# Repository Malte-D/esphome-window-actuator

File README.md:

# ESPHome Tilt Window Opener

<p align="center">

</p>

Motorise an ordinary **tilt-and-turn window** (German: *Dreh-Kipp-Fenster*) with two
3D-printed units, two 12 V servos (DSSERVO DS51150, 150 kg·cm) and an ESP8266 running [ESPHome](https://esphome.io).
The window shows up in Home Assistant as a `cover` and can be tilted open and closed
again, including turning the handle. No drilling: the handle unit uses the original
handle screws and the top unit is hot-glued.

<p align="center">
  
  <br/>
  <sub>Rendered animation. The inset shows the handle unit cut open, then the linkage at the top of the sash.
  <a href="docs/media/demo.mp4">Full resolution video</a></sub>
</p>

> **Status: v0.1.** The hardware and firmware have been in daily use for more than a year.
> Places that still need a value are marked **TBD**; values marked *(estimate)* were derived from
> the CAD files and still need to be confirmed.

## Features

- Tilts the window open and closes it again from Home Assistant (`cover` entity, device class `window`)
- Turns the handle by itself: closed ↔ tilt, plus a "fully open" (turn) position
- Servo power is switched by a relay only while something moves: no humming or holding current when idle
- Maintenance mode to calibrate every end position from Home Assistant; values are stored on the device
- Bayonet quick release in the linkage, so the window can still be opened completely by hand
- Hot glue on the top unit doubles as a breakaway point if something jams
- Firmware can be flashed from the browser (ESP Web Tools) and adopted in the ESPHome dashboard

## How it works

The opener consists of two units on the sash, connected by a servo cable:

| | Handle unit | Top unit |
|---|---|---|
| Replaces / sits on | the window handle | the top rail of the sash |
| Servo | DS51150, 150 kg·cm, 12 V, **270° version** | DS51150, 150 kg·cm, 12 V, 180° or 270° version |
| Moves | the 7 mm square spindle of the window gear | an 80 mm arm, linked to a pivot glued into the corner between frame and lintel |
| Also contains | the [PCB](pcb/README.md) (Wemos D1 mini, relay, 5 V step-down converter) | – |

The original handle is removed. A short 7 mm square spindle goes from the window gear into
the **ServoHornAdapter**, which is screwed onto the servo horn on the same axis, so the servo
turns the spindle directly, like a hand on the handle. The handle servo is the 270° version of the DS51150:
the handle only needs 180°, the rest is margin for adjusting the end positions in software.

At the top, the servo arm and a short coupler with two rod ends (uniball joints) form a linkage
to a fixed pivot. When the arm swings round, it pushes the top of the sash into the room, and the
window tilts. The coupler is a printed bayonet, so the window can be disconnected from the arm
and opened completely by hand.

Sequence (see [`window-actuator-template-esp8266.yaml`](window-actuator-template-esp8266.yaml)):

| Open | Close |
|---|---|
| 1. Relay on (servo power) | 1. Relay on |
| 2. Handle servo → tilt position (3 s) | 2. Arm servo → closed position (2 s) |
| 3. Arm servo → open position (2 s) | 3. Handle servo → closed position (3 s) |
| 4. Relay off | 4. Relay off |

## What you need

### Window

A standard tilt-and-turn window with the usual handle fixing: two screws 43 mm apart and a
7 mm square spindle; handle down = closed, horizontal = turn, up = tilt. The top unit needs a
bit of visible frame between the top of the sash and the lintel for the arm and the pivot mount.

### Printed parts

All parts are in [`print-files/`](print-files) as STEP and (mostly) 3MF.

| Part | Folder | Qty | Notes |
|---|---|---|---|
| Base | `Handle` | 1 | Mounts with the original handle screws. 3MF: **TBD** |
| Case | `Handle` | 1 | Holds the handle servo and the PCB holder |
| ServoCover | `Handle` | 1 | Snaps onto the two CoverSnaps |
| CoverSnap | `Handle` | 2 | Clamped under the servo screws |
| PCBHolder | `Handle` | 1 | Slides into the slot at the edge of the base. 3MF: **TBD** |
| ServoHornAdapter | `Handle` | 1 | Square spindle → servo horn |
| ServoCoverMount | `Movement` | 1 | Housing for the arm servo, hooks over the top rail of the sash |
| NutHolder | `Movement` | 2 | Holds the M3 nuts behind the servo flange |
| ServoArm | `Movement` | 1 | 80 mm from servo axis to the M6 bolt |
| TopPivotMount *or* TopPivotMountChamfered | `Movement` | 1 | Pivot in the corner between frame and lintel. Use the chamfered version (45°) if that corner is not a clean right angle |
| BayonetSocket + BayonetPlug | `Movement` | 1 each | Quick release between the two rod ends. Both have a printed M6 thread for the rod ends |
| CableDuctCorner | `Accessories` | 2 | Corner for 16 × 8 mm half-round cable duct; the spigots go into the duct ends. One per bend, see [wiring](docs/assembly.md#6-wiring) |

The 3MF files contain only the geometry, no printer or slicer settings.

- **Material:** PLA is enough, even on a window in the sun.
- **Settings** *(estimate)*: 0.2 mm layers, 4 walls, 30–40 % infill for the parts that carry the
  servo torque (Base, Case, ServoHornAdapter, ServoArm, ServoCoverMount, bayonet), 20 % for the rest.
- Supports only where the slicer finds real overhangs; keep nut traps and slots free of support.

### Electronics

| Qty | Part | Notes |
|---|---|---|
| 2 | Servo **DSSERVO DS51150** (150 kg·cm, 12 V), e.g. [this one on AliExpress](https://www.aliexpress.com/item/1005006896077837.html) | 270° version for the handle; for the arm 180° is enough. The 12 V supply is why the 150 kg version is used: the smaller ones are specified below 12 V. The servo horn that comes with it is used |
| 1 | Custom PCB, 35 × 60 mm, with a Wemos D1 mini, a 5 V relay for the servo power and a 12 V → 5 V step-down converter | Gerbers, design files and parts list in [`pcb/`](pcb/README.md) |
| 1 | 12 V power supply, 5 A, standard plug 5.5 × 2.1 mm, centre positive | The prototype runs on a 12 V / 5 A supply. An angled plug fits best under the case |
| 1 | Servo extension cable | From the handle unit to the top unit (top centre of the sash); length depends on the window |
| – | Cable duct, half-round, 16 × 8 mm | Along the sash for both cables, see [wiring](docs/assembly.md#6-wiring). The prototype uses white D-Line duct with the printed CableDuctCorner at the bends |

### Hardware

| Qty | Part | Where |
|---|---|---|
| 1 | 7 mm square spindle, 50 mm on the prototype; the length depends on the window, see [below](#spindle-length) | Window gear → ServoHornAdapter |
| 2 | Original handle screws | Base → sash |
| 3 | M4×16 countersunk | Case → Base (from the side) |
| 3 | M4 square nut, DIN 562 (7 × 7 × 2.2 mm) | Slots in the base |
| 8 | M3×25 | 4 per servo: handle servo and CoverSnaps → Case, arm servo → ServoCoverMount |
| 8 | Rubber grommets, come with the servos | In the flange slots of both servos, to decouple vibrations |
| 8 | M3 nut | 4 in the case, 2 in each NutHolder |
| 4 | M3×10 countersunk | Servo horns (2 on the adapter, 2 on the arm) |
| 1 | M3×10 | PCB → PCBHolder |
| 2 | M6 rod end / uniball joint with male thread (e.g. SA6T/K or POSA6) | Screwed into the bayonet socket and plug |
| 1 | M6×25 + M6 nut | Rod end → ServoArm |
| 1 | M4×16 + M4 washer + M4 nut | Rod end → pin of the TopPivotMount |
| 1 | O-ring 10 × 2 mm | On the stem of the bayonet plug, keeps the bayonet locked |
| – | Hot glue | ServoCoverMount → sash, TopPivotMount → frame and lintel |

The servo horns are the ones that come with the DS51150 servos.

#### Spindle length

The spindle has to stick out about **21–25 mm from the surface of the sash** (where the handle
rosette was) *(estimate)*: the square hole in the ServoHornAdapter starts about 13 mm above the sash
and is 12.8 mm deep. These values come from the CAD files, a model of the DS51150 and the measured
7.5 mm between case and CoverSnap (rubber grommets under the servo flange), not from a measurement
of the spindle itself. How far the spindle goes into the window depends on the window. The prototype uses a
50 mm spindle; a longer one can be cut to length.

## Assembly

See the step-by-step guide in **[docs/assembly.md](docs/assembly.md)**.

## Firmware

### Install

1. Open the [installer page](https://malte-d.github.io/esphome-tilt-window-opener/) in Chrome or Edge,
   connect the D1 mini via USB and click **Install**.
2. Enter your Wi-Fi credentials in the installer (Improv). Alternatively, the device opens a
   fallback hotspot `window-actuator-xxxxxx`; its password is set in the YAML (`wifi.ap.password`).
3. Home Assistant discovers the device. To customise the firmware, adopt it in the ESPHome dashboard,
   which imports [`window-actuator-template-esp8266.yaml`](window-actuator-template-esp8266.yaml).

### Pins

| D1 mini pin | Function |
|---|---|
| D1 (GPIO5) | Arm servo signal (`servo_movement`) |
| D3 (GPIO0) | Handle servo signal (`servo_handle`) |
| D2 (GPIO4) | Relay that switches the 12 V servo supply |

### Entities

| Entity | Type | Purpose |
|---|---|---|
| Window | cover | Open (tilt) / close |
| Maintenance Mode | switch | Blocks open/close and enables the manual buttons below |
| Servo Handle Close / Open / Fully Open Position | number | Handle servo positions for closed, tilt and turn (−100 … 100) |
| Servo Movement Open / Close Position | number | Arm servo positions (−100 … 100) |
| manual_handle_close / _open / _fully_open | button | Move the handle servo (maintenance mode only) |
| manual_movement_open / _close | button | Move the arm servo (maintenance mode only) |
| relay_on / relay_off | button | Switch the servo supply (maintenance mode only) |
| home | button | Mark the window as closed without moving anything, e.g. after it was closed by hand |

The value range −100 … 100 covers the full servo travel (pulse 0.5–2.5 ms).
Defaults: handle closed `65`, tilt `-72`, turn `0`; arm open `68`, closed `-100`.

### Calibration

1. Turn on **Maintenance Mode**. The number entities now show the stored positions.
2. Press **relay_on** to power the servos.
3. Handle: set *Servo Handle Close Position* and press **manual_handle_close**. Adjust until the
   handle is exactly in the closed position. Repeat for *Open* (tilt, **manual_handle_open**) and
   *Fully Open* (turn, **manual_handle_fully_open**).
4. Turn the handle to **tilt** first, then set the arm with *Servo Movement Close/Open Position*
   and **manual_movement_close / _open**.
5. Press **relay_off** and turn Maintenance Mode off. Positions survive reboots.

> ⚠️ Only move the arm while the handle is in the tilt position. With the handle closed, the arm
> pushes against the locked sash with full servo force.

### Opening the window by hand

To open the window completely, e.g. for cleaning:

1. Maintenance Mode on, **relay_on**, **manual_handle_fully_open**: the handle is now in the turn position.
2. Release the bayonet coupler at the top: push the two halves together, turn back, pull apart.
3. Open the window by hand.

<p align="center">
  
  <br/>
  <sub>The bayonet coupler, socket drawn transparent. <a href="docs/media/bayonet.mp4">Video</a></sub>
</p>

To go back, close the window, press **manual_handle_close**, reconnect the coupler, press
**relay_off**, turn Maintenance Mode off and press **home** if Home Assistant shows the wrong state.

## Safety

- The servos are strong (DS51150, 150 kg·cm). Keep fingers away from the arm, the coupler and the handle
  unit while the servos are powered.
- The hot-glued top unit is meant to break off before the window or the frame gets damaged.
  Check it from time to time.
- An open window lets in rain and is an easy way into the house. Use automations accordingly,
  e.g. close the window when it starts to rain or when nobody is home.

## Renders and animation

The pictures in `docs/` and the demo animation are rendered from the STEP files with Blender.
The scripts live in [`tools/render/`](tools/render/README.md), so everything can be re-rendered
once parts change.

## License

**TBD**

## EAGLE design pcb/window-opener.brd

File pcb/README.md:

# PCB

A small two-layer board (35 × 60 mm, 1.6 mm) that carries the Wemos D1 mini, switches the servo
power and connects both servos. It sits on the PCBHolder in the handle unit (1× M3×10).

## Files

| File | What it is |
|---|---|
| [`gerber/window-opener-v26-gerber.zip`](gerber/window-opener-v26-gerber.zip) | Gerber and drill files, revision v26, the board in use (ordered from JLCPCB in 2024). Upload this zip to any PCB manufacturer |
| [`window-opener.sch`](window-opener.sch), [`window-opener.brd`](window-opener.brd) | Schematic and board, EAGLE 9.7 format. Open them in Fusion Electronics or EAGLE, or import them into KiCad |

The design files are newer than the Gerbers: they add two optional 0 Ω bridges (R3, R4) on the
bottom of the board, which the v26 board does not have. What they are for: **TBD**.

## Circuit

- **12 V in:** DC jack 5.5 × 2.1 mm, centre positive.
- **5 V:** a small step-down converter makes 5 V from the 12 V for the D1 mini and the relay coil.
  It is a 3-pin module that fits the TO-220 footprint of a 7805 (IN, GND, OUT), e.g.
  [this one on AliExpress](https://www.aliexpress.com/item/1005006579355456.html). The board files show an LM7805 there as a placeholder. A real
  LM7805 would also work, but it turns the 7 V difference into heat inside the closed case.
- **Servo power:** D2 switches the relay through an N-channel MOSFET (100 Ω gate resistor,
  10 kΩ pull-down). The relay connects the 12 V to the + pin of both servo headers, so the
  servos only get power while the window moves.
- **Servo signals:** D3 → handle servo (JP1), D1 → arm servo (JP2).
- **Spare pins:** JP3 brings out A0, D0, D5–D8, 3V3 and GND. They are not used by the firmware.

## Connectors

| Header | Silkscreen | Connect | Pin order |
|---|---|---|---|
| JP1 | D3 | Handle servo | − + S (brown, red, orange) |
| JP2 | D1 | Arm servo (via the extension cable) | − + S (brown, red, orange) |
| 12V | – | 12 V power supply, 5 A | centre positive |

## Parts

| Ref | Qty | Part | Package |
|---|---|---|---|
| WEMOS2 | 1 | Wemos D1 mini (ESP8266), with its two 8-pin headers | module |
| U$1 | 1 | Relay SRD-05VDC-SL-C (5 V coil, 10 A contacts) | THT |
| IC1 | 1 | Step-down converter module 12 V → 5 V, pin-compatible with a 7805, e.g. [this one](https://www.aliexpress.com/item/1005006579355456.html). Pin order on the board, left to right as printed: 5V, GND, 12V; check the IN/OUT marks on the module | 3 pins, 2.54 mm, upright |
| 12V | 1 | DC jack 5.5 × 2.1 mm, Würth 694106301002 | THT |
| Q1 | 1 | N-channel MOSFET, logic level (type used: **TBD**, e.g. AO3400A) | SOT-23 (G-S-D) |
| R1 | 1 | 100 Ω | 0805 |
| R2 | 1 | 10 kΩ | 0805 |
| JP1, JP2 | 2 | Pin header 1×3, 2.54 mm | THT |
| JP3 | 1 | Pin header 1×8, 2.54 mm (optional) | THT |

The three SMD parts are large enough (0805, SOT-23) to solder by hand.

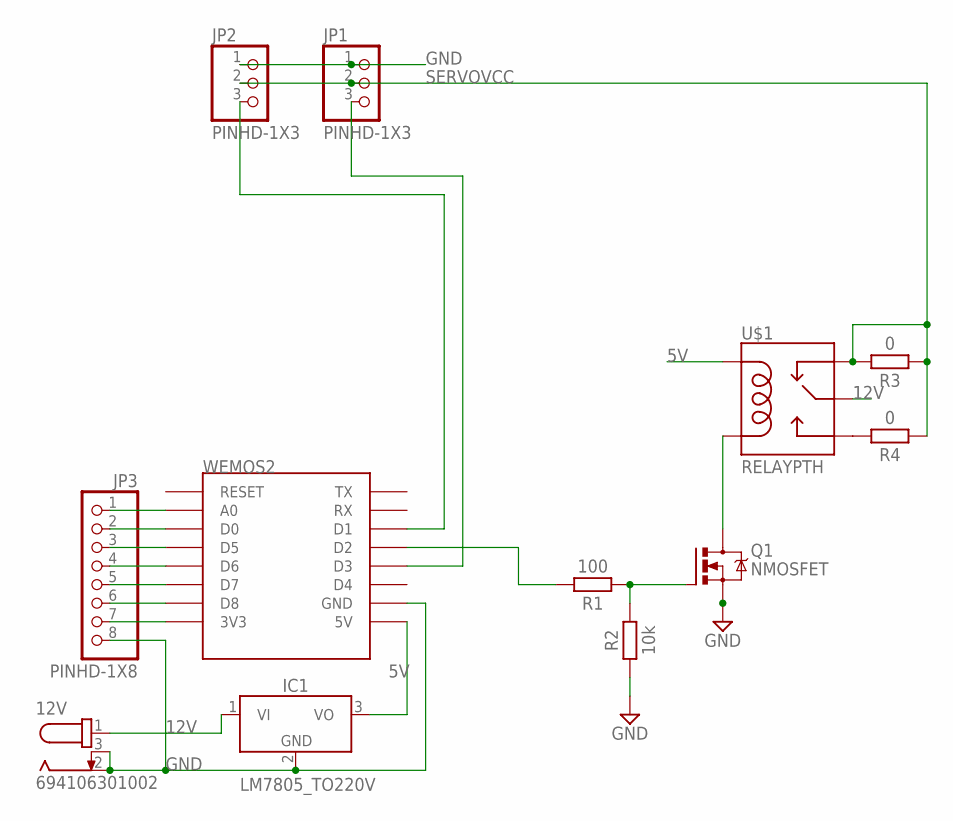
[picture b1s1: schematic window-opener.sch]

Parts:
12V: 694106301002
IC1: LM7805_TO220V; TO220V
JP1, JP2: PINHD-1X3; 1X03
JP3: PINHD-1X8; 1X08
Q1: NMOSFET; SOT23
R1: 100; RESC2012X65
R2: 10k; RESC2012X65
R3, R4: 0; RESC2012X65
U$1: RELAYPTH; SRD-05VDC-SL-C
WEMOS2: WEMOS-D1-MINI

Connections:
5V: IC1.3 (VO), U$1.COIL1, WEMOS2.5V
12V: 12V.1, IC1.1 (VI), U$1.SWCOMMON
GND: 12V.2, 12V.3, IC1.2 (GND), JP1.1, JP2.1, JP3.8, Q1.2 (S), R2.1, WEMOS2.GND
unnamed: Q1.1 (G), R1.1, R2.2
unnamed: JP2.3, WEMOS2.D1
unnamed: JP3.1, WEMOS2.A0
unnamed: JP1.3, WEMOS2.D3
unnamed: R1.2, WEMOS2.D2
unnamed: JP3.2, WEMOS2.D0
unnamed: JP3.3, WEMOS2.D5
unnamed: JP3.4, WEMOS2.D6
unnamed: JP3.5, WEMOS2.D7
unnamed: JP3.6, WEMOS2.D8
unnamed: JP3.7, WEMOS2.3V3
unnamed: R4.2, U$1.SWOPEN
R: Q1.3 (D), U$1.COIL0
SERVOVCC: JP1.2, JP2.2, R3.1, R3.2, R4.1, U$1.SWCLOSED (SWCLOSE)

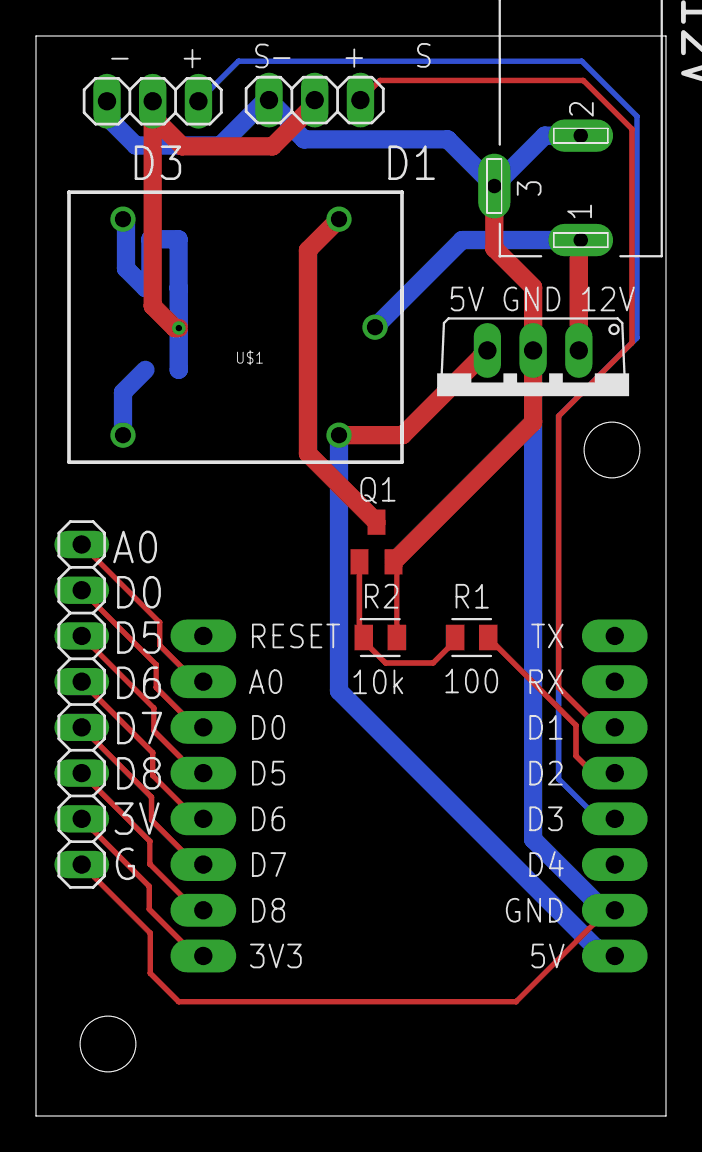
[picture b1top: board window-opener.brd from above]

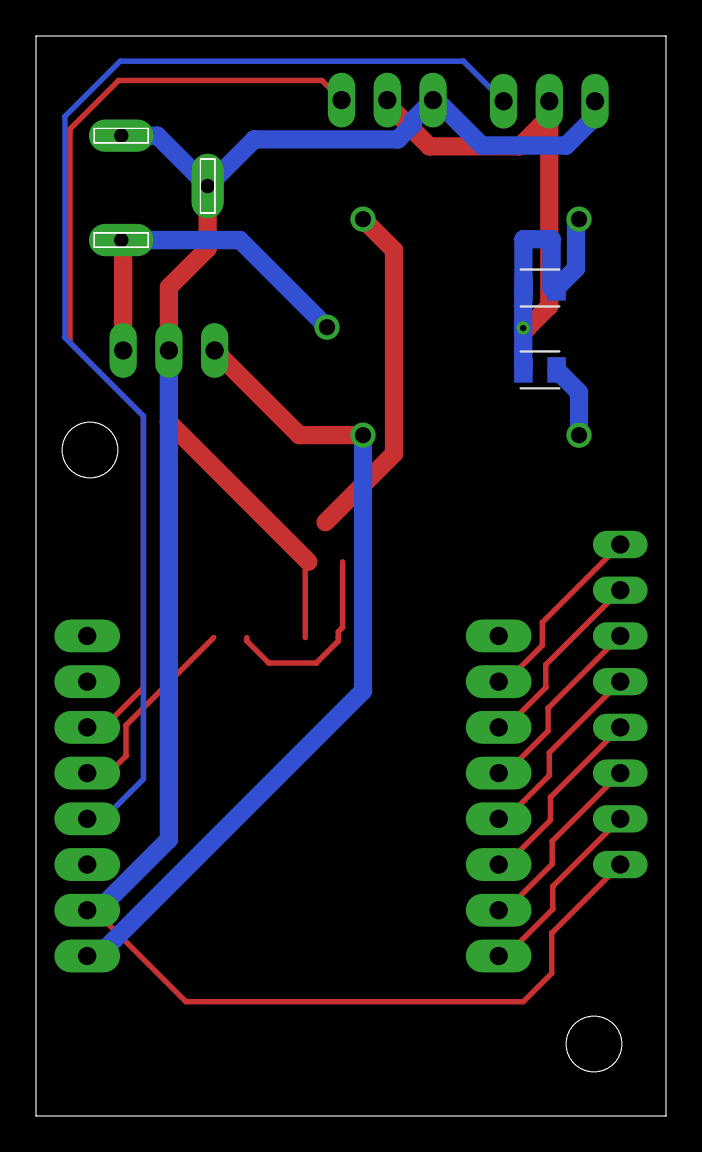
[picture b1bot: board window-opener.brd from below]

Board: 2 copper layers, 35.0 x 60.0 mm, 12 parts (2 on the bottom side), 17 nets.

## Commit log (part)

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2024-05-25 Rename project-template-esp8266.yaml to window-actuator-template-esp8266.yaml
2024-05-25 Initial gh-pages commit
2024-05-25 Deploying to gh-pages from @ Malte-D/esphome-window-actuator@1a1a3c3facca7ccbc82ee9bd778b14f6ec59e3f7 🚀
2024-05-25 Deploying to gh-pages from @ Malte-D/esphome-window-actuator@c751b9b38f6a78b73bc34e9117d9194741516193 🚀
2024-05-25 Deploying to gh-pages from @ Malte-D/esphome-window-actuator@fcc740d1ae12747e52525af0d141978b5c9fdecb 🚀
2024-05-25 Deploying to gh-pages from @ Malte-D/esphome-window-actuator@7b0473fbf0ddb7c991e440de2554a00456b54994 🚀
2024-06-02 Deploying to gh-pages from @ Malte-D/esphome-window-actuator@e851ce650e1b41aaf62fe89ba65a1dc4ca17ebfb 🚀
2024-06-02 Deploying to gh-pages from @ Malte-D/esphome-window-actuator@8c9f17238a1601cd8f11559193f162776ea52433 🚀
2024-10-17 Deploying to gh-pages from @ Malte-D/esphome-window-actuator@e6a2f810b344efb7078c9c61534f1c71db1e6c70 🚀
2024-10-17 Deploying to gh-pages from @ Malte-D/esphome-window-actuator@f3c0aa538fd8da89f2fc6372b6a8d3d9f95dc23d 🚀
2024-10-17 Deploying to gh-pages from @ Malte-D/esphome-window-actuator@8c046ca7a1178b0a08ac7f78c759c01c23cd3aa5 🚀
2024-10-17 Deploying to gh-pages from @ Malte-D/esphome-window-actuator@824b0afe39db6456e995f680c96323aa909af724 🚀
2024-10-17 Deploying to gh-pages from @ Malte-D/esphome-window-actuator@fdeef59d61fe153c874f3eab811e1ab0feee1b49 🚀
2024-10-17 Deploying to gh-pages from @ Malte-D/esphome-window-actuator@d9b86d70585e2128c5b473dbd048bb2cc1520874 🚀
2024-10-17 Deploying to gh-pages from @ Malte-D/esphome-window-actuator@9b96bbab6d0dc26fc6340bd38d69ae112c3caf6f 🚀
2024-11-02 Deploying to gh-pages from @ Malte-D/esphome-window-actuator@2a903af008d740988f969ccd17546c4d0453e6ec 🚀
2024-11-02 Deploying to gh-pages from @ Malte-D/esphome-window-actuator@789ab7cc128a1a52d049817fe9f639f9e2cd556a 🚀
2024-11-02 Deploying to gh-pages from @ Malte-D/esphome-window-actuator@5d94f29c11ab1d9672b0e11b30aba52711a1ad33 🚀
2024-11-02 Deploying to gh-pages from @ Malte-D/esphome-window-actuator@3a5dc1de7554f53cf9167997fa98dacf582f0b13 🚀
2024-11-02 Deploying to gh-pages from @ Malte-D/esphome-window-actuator@3553d65237dd0665af890d28d42a486e2c2ced12 🚀
2024-11-02 Deploying to gh-pages from @ Malte-D/esphome-window-actuator@f61302293a6e9df6b9a290ba3b771a819e7179c0 🚀
2024-11-02 Deploying to gh-pages from @ Malte-D/esphome-window-actuator@cfaa716472ef3efbcd70ee41909b0a93c78ef7d8 🚀
2024-11-02 Deploying to gh-pages from @ Malte-D/esphome-window-actuator@6c6060b29ce270d251157387b9a6fb83a10fb3c8 🚀
2024-11-02 Deploying to gh-pages from @ Malte-D/esphome-window-actuator@a8ca54e3f7fece68316748a4782a1941fbc575b5 🚀
2024-11-03 Deploying to gh-pages from @ Malte-D/esphome-window-actuator@f8de6206fcf667e0926826170a915fda97f19489 🚀
2024-11-03 Deploying to gh-pages from @ Malte-D/esphome-window-actuator@b54ca0d42a821abba9c2e39e15512100f1d0f508 🚀
2024-11-03 Deploying to gh-pages from @ Malte-D/esphome-window-actuator@895e4cb875676381a942027ec2b610cad0565cb6 🚀
2024-11-03 Deploying to gh-pages from @ Malte-D/esphome-window-actuator@052fcd4d263b47f704cc974c4a80c637d61d802e 🚀
2024-11-03 Deploying to gh-pages from @ Malte-D/esphome-window-actuator@4d3ada2a9ccf7f031d90745ae6325fe99a10be85 🚀
2024-11-03 Deploying to gh-pages from @ Malte-D/esphome-window-actuator@ab1b58a27f8789c3cc2b1bdf5ef09d39a34d6a9e 🚀
2024-11-03 Deploying to gh-pages from @ Malte-D/esphome-window-actuator@5c1703d735c4a92d02a2280db353773c8fc6d921 🚀
2024-11-03 Deploying to gh-pages from @ Malte-D/esphome-window-actuator@223f1d82195c96650a17c24fb76f26650078132d 🚀
2024-11-10 Deploying to gh-pages from @ Malte-D/esphome-window-actuator@f39efbf8f6bf6a49fc6094ccbc95459f78101eae 🚀
2025-03-17 added some print files
2025-11-30 Updated ServoHornAdapter
